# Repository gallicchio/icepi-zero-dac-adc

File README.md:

# FPGA tutorials: an ADC and a DAC on an Icepi Zero

A hands-on tutorial for a junior-level physics electronics lab. You should
know basic analog and digital electronics and a little Fourier analysis. You
do **not** need to have seen an [FPGA](https://en.wikipedia.org/wiki/Field-programmable_gate_array) or a hardware description language
before.

You will:

* configure the logic inside an FPGA to **blink lights**, **make analog
  waveforms** and **capture analog signals** at 25 million samples a second;
* build a **[lock-in amplifier](https://en.wikipedia.org/wiki/Lock-in_amplifier)** and use it as a simple [network analyzer](https://en.wikipedia.org/wiki/Network_analyzer_(electrical)), and
  a **[spectrum analyzer](https://en.wikipedia.org/wiki/Spectrum_analyzer)**, with an FFT computed in logic;
* build an **AM radio**, transmitter and receiver, and hear it on a real radio
  and on your laptop;
* turn the same FPGA into a **[RISC-V](https://en.wikipedia.org/wiki/RISC-V) computer** and write C programs that run
  on it and talk to your hardware;
* boot **Linux** on that computer, and read the [ADC](https://en.wikipedia.org/wiki/Analog-to-digital_converter) as an ordinary file;
* and then, if you like, keep going: crystals, resonators, the speed of sound,
  [time transfer](https://en.wikipedia.org/wiki/Time_transfer) between two boards (as national labs do it), modern
  digital communications (OFDM, at 56 Mbit/s through a cable), and a radio
  link.

Everything is open source, from the FPGA tools to the instruments: an
open-source function generator, digitizer (a slow oscilloscope), lock-in
amplifier, network analyzer, FFT spectrum analyzer, AM transmitter and
software-defined radio receiver, modems, and a time-transfer link, each a
page or two of SystemVerilog and Python that you can read and change.
[5.08](tutorial/5_08_more_hardware.md#instruments-for-a-physics-lab) lists more
that physics labs usually buy: a [Pound–Drever–Hall](https://en.wikipedia.org/wiki/Pound%E2%80%93Drever%E2%80%93Hall_technique) laser lock, a
coincidence counter, shot-noise and Johnson-noise measurements.

Most people will get as far as the lock-in amplifier
([1.08](tutorial/1_08_lockin.md#108-a-lock-in-amplifier)), and that's a fine
place to stop. Each later chapter builds on the earlier ones, but you can
skip around inside Chapters 4 and 5. The hardware is about $120:
[0.00](tutorial/0_00_the_hardware.md#000-the-hardware) has the list, and
[Appendix A](tutorial/A_why_this_hardware.md#appendix-a-why-this-hardware)
the prices.

**Start here: [0.00 The hardware](tutorial/0_00_the_hardware.md#000-the-hardware).**

## What depends on what

Nothing after Chapter 1 needs all of Chapter 1, and nothing needs Linux
except the two pages that use it. The spine is 1.00–1.08: the tools, a
counter, the [DAC](https://en.wikipedia.org/wiki/Digital-to-analog_converter), a sine, the ADC into Python, fast captures, the loopback,
and the lock-in. After that, go where you like:

```mermaid
flowchart LR
  spine["<b>Chapter 1, the spine</b><br/>1.00–1.08: tools, DAC, ADC,<br/>loopback, lock-in"]
  fft["1.09 FFT spectrum analyzer"]
  am["1.10 AM radio"]
  c2["<b>2. A processor</b><br/>LiteX, C, your peripherals"]
  c3["<b>3. Linux</b>"]
  c4["<b>4. One-board experiments</b><br/>(4.01 needs only 1.03)"]
  c5["<b>5. Two boards</b>"]
  c6["<b>6. Digital communications</b>"]
  c7["<b>7. Signal processing in gateware</b><br/>filters, delta-sigma, control"]
  spine --> fft
  spine --> am
  spine --> c2 --> c3
  spine --> c4
  spine --> c5
  spine --> c6
  spine --> c7
  c2 -. "7.04's LiteX peripheral" .-> c7
  c6 -. "6.11's modem is the warm-up" .-> c7
  fft -. "6.07's OFDM" .-> c6
  c5 -. "awgcap.sv: just load it (6.00)" .-> c6
  c5 -. "5.07's loops, for 6.12's air" .-> c6
  c5 -. "5.05's network between two Linuxes" .-> c3
  c2 -. "2.00's tool install, then 3.01 boots the prebuilt Linux" .-> c3
```

The shortest paths:

- **The lock-in amplifier:** 1.00–1.08. (1.04 is optional; 1.09 and 1.10 are desserts.)
- **Digital communications (Chapter 6):** the spine, then [6.00](tutorial/6_00_digital_communications.md#600-digital-communications-hardware-defined-radio). It uses one
  design from Chapter 5, `awgcap.sv`, which you load without reading the chapter. One board is enough.
- **Linux on the FPGA:** 1.00–1.01 (load a bitstream), [2.00](tutorial/2_00_a_processor_on_the_fpga.md#200-a-processor-on-the-fpga) (install LiteX), then
  [3.01](tutorial/3_01_booting_linux.md#301-booting-linux) boots the prebuilt images. Understanding the driver ([3.02](tutorial/3_02_a_driver.md#302-a-driver)) wants 2.03–2.05;
  building it all yourself ([3.03](tutorial/3_03_building_linux.md#303-building-linux-yourself)) wants Chapter 2.
- **Filters, delta-sigma and control (Chapter 7):** the spine, then [7.00](tutorial/7_00_signal_processing_in_gateware.md#700-signal-processing-in-gateware); 7.04 alone needs Chapter 2's tools.
- **The experiments (Chapter 4):** the spine; each page says which instrument it uses.
- **Two boards (Chapter 5):** the spine and a second board; only the network part of
  [5.05](tutorial/5_05_fsk_modem.md#505-a-modem) needs Chapter 3.

Every chapter opener (2.00, 3.00, 4.00, 5.00, 6.00) starts with "What you need
first", so you can check before you start.

## Related reading

- **[learnSDR](https://github.com/gallicchio/learnSDR)**, this author's video course in software-defined radio with
  GNU Radio: Chapter 6 links its lessons.
- **[PySDR](https://pysdr.org)**, Marc Lichtman's free online textbook of SDR and DSP in Python. It is
  better than these pages at the theory and the Python, and it covers what this tutorial
  can't (link budgets, beamforming, real SDR hardware); read it alongside Chapter 6. What
  this tutorial has that it doesn't is that the hardware is yours, down to the clock.
- **[MIT's coffee-can radar course](https://ocw.mit.edu/courses/res-ll-003-build-a-small-radar-system-capable-of-sensing-range-doppler-and-synthetic-aperture-radar-imaging-january-iap-2011/)**, the model for the radar chapter sketched in [6.13](tutorial/6_13_more_ideas.md#613-more-ideas-and-a-radar-chapter).

## Contents

**0. Getting started**

- [0.00 The hardware](tutorial/0_00_the_hardware.md)
- [0.01 How to use this tutorial](tutorial/0_01_how_to_use_this_tutorial.md)

**1. Logic in [SystemVerilog](https://en.wikipedia.org/wiki/SystemVerilog), up to a lock-in amplifier and an FFT**

- [1.00 Circuits from code](tutorial/1_00_circuits_from_code.md)
- [1.01 A counter on the LEDs](tutorial/1_01_led_counter.md)
- [1.02 A sawtooth from the DAC](tutorial/1_02_dac_sawtooth.md)
- [1.03 A sine: direct digital synthesis](tutorial/1_03_dac_sine.md)
- [1.04 The ADC on the LEDs](tutorial/1_04_adc_on_the_leds.md)
- [1.05 ADC samples to Python](tutorial/1_05_adc_to_python.md)
- [1.06 Fast captures](tutorial/1_06_fast_capture.md)
- [1.07 Closing the loop: the DAC talks to the ADC](tutorial/1_07_closing_the_loop.md)
- [1.08 A lock-in amplifier](tutorial/1_08_lockin.md)
- [1.09 A spectrum analyzer](tutorial/1_09_spectrum_analyzer.md)
- [1.10 An AM radio](tutorial/1_10_am_radio.md)

**2. A RISC-V processor, and C**

- [2.00 A processor on the FPGA](tutorial/2_00_a_processor_on_the_fpga.md)
- [2.01 A CPU and its BIOS](tutorial/2_01_a_cpu_and_its_bios.md)
- [2.02 C on the CPU](tutorial/2_02_c_on_the_cpu.md)
- [2.03 A function-generator peripheral](tutorial/2_03_function_generator_peripheral.md)
- [2.04 A capture peripheral](tutorial/2_04_capture_peripheral.md)
- [2.05 A lock-in peripheral](tutorial/2_05_lockin_peripheral.md)
- [2.06 The registers from the laptop](tutorial/2_06_registers_from_the_laptop.md)

**3. Linux**

- [3.00 Linux on the FPGA](tutorial/3_00_linux_on_the_fpga.md)
- [3.01 Booting Linux](tutorial/3_01_booting_linux.md)
- [3.02 A driver](tutorial/3_02_a_driver.md)
- [3.03 Building Linux yourself](tutorial/3_03_building_linux.md)
- [3.04 Booting from an SD card](tutorial/3_04_booting_from_sd.md)

**4. More experiments with one board**

- [4.00 One-board experiments](tutorial/4_00_one_board_experiments.md)
- [4.01 A faster DAC: PLLs](tutorial/4_01_a_faster_dac.md)
- [4.02 RC and LC circuits](tutorial/4_02_rc_and_lc_circuits.md)
- [4.03 The Q of a quartz crystal](tutorial/4_03_quartz_crystal.md)
- [4.04 Harmonics: a diode clipper](tutorial/4_04_harmonics.md)
- [4.05 A quarter-wave stub](tutorial/4_05_quarter_wave_stub.md)
- [4.06 The speed of sound at 40 kHz](tutorial/4_06_speed_of_sound.md)
- [4.07 An optical link](tutorial/4_07_optical_link.md)
- [4.08 Feedback control of an RC plant](tutorial/4_08_feedback_control.md)
- [4.09 Your crystal against a reference](tutorial/4_09_your_crystal.md)
- [4.10 More ideas for one board](tutorial/4_10_more_ideas.md)

**5. Two boards**

- [5.00 Two boards on one laptop](tutorial/5_00_two_boards.md)
- [5.01 Two clocks](tutorial/5_01_two_clocks.md)
- [5.02 Warming a crystal](tutorial/5_02_warming_a_crystal.md)
- [5.03 What time is it over there?](tutorial/5_03_time_transfer.md)
- [5.04 Oscillators that listen to each other](tutorial/5_04_coupled_oscillators.md)
- [5.05 A modem](tutorial/5_05_fsk_modem.md)
- [5.06 The modem against noise](tutorial/5_06_modem_and_noise.md)
- [5.07 A radio link](tutorial/5_07_radio_link.md)
- [5.08 With a little more hardware](tutorial/5_08_more_hardware.md)

**6. Digital communications (Hardware Defined Radio)**

- [6.00 Digital communications (Hardware Defined Radio)](tutorial/6_00_digital_communications.md)
- [6.01 Eye diagrams and pulse shaping](tutorial/6_01_eye_diagrams.md)
- [6.02 PSK and QPSK: finding the clock and the carrier](tutorial/6_02_psk_and_qpsk.md)
- [6.03 QAM: more bits per symbol](tutorial/6_03_qam.md)
- [6.04 MSK and GMSK: constant envelope](tutorial/6_04_msk_and_gmsk.md)
- [6.05 The channel: sounding it, and equalizing it](tutorial/6_05_the_channel.md)
- [6.06 Spread spectrum, the GPS way](tutorial/6_06_spread_spectrum.md)
- [6.07 OFDM: the triumph of physics over math](tutorial/6_07_ofdm.md)
- [6.08 Shannon's limit, and how far from it you are](tutorial/6_08_shannons_limit.md)
- [6.09 Error-correcting codes](tutorial/6_09_error_correcting_codes.md)
- [6.10 Chirps, Zadoff–Chu and LoRa: ranging, and radar on a cable](tutorial/6_10_chirps_and_lora.md)
- [6.11 The modem in the FPGA](tutorial/6_11_the_modem_in_the_fpga.md)
- [6.12 On the air: whispers, and how far they carry](tutorial/6_12_on_the_air.md)
- [6.13 More ideas, and a radar chapter](tutorial/6_13_more_ideas.md)

**7. Signal processing in gateware**

- [7.00 Signal processing in gateware](tutorial/7_00_signal_processing_in_gateware.md)
- [7.01 FIR filters: the sliding dot product](tutorial/7_01_fir_filters.md)
- [7.02 IIR filters: feedback, and an RC in one line](tutorial/7_02_iir_filters.md)
- [7.03 A filter you can load](tutorial/7_03_a_filter_you_can_load.md)
- [7.04 The filter as a LiteX peripheral](tutorial/7_04_the_filter_as_a_litex_peripheral.md)
- [7.05 Trading speed for bits](tutorial/7_05_trading_speed_for_bits.md)
- [7.06 Control at the speed of the cable](tutorial/7_06_control.md)
- [7.07 Bigger ideas: NMR, MRI and qubits](tutorial/7_07_bigger_ideas.md)

**Appendices**

- [Appendix A. Why this hardware?](tutorial/A_why_this_hardware.md)
- [Appendix B. Troubleshooting](tutorial/B_troubleshooting.md)
- [Appendix C. How this tutorial was tested](tutorial/C_how_it_was_tested.md)
- [Appendix D. Coming soon… hopefully](tutorial/D_coming_soon.md)

## What's in this repository

| folder | what |
| --- | --- |
| [`tutorial/`](tutorial/) | the tutorial, one page per topic, in order |
| [`src/`](src/) | everything you build: [`verilog/`](src/verilog/) (Chapters 1 and 4), [`riscv/`](src/riscv/) (Chapter 2), [`linux/`](src/linux/) (Chapter 3), [`twoboard/`](src/twoboard/) (Chapter 5, and 6.11's `qpsk_modem.sv` and 6.12's `ddc.sv`), [`comms/`](src/comms/) (Chapter 6's Python), [`dsp/`](src/dsp/) (Chapter 7) |
| [`adapter_board/`](adapter_board/) | the adapter PCB between the Icepi Zero and the converter module: KiCad files and gerbers, ready to order |
| [`dev/`](dev/) | how the tutorial was made and tested: measurement scripts, raw data, and the log of the Claude Code sessions that wrote it |
| [`LICENSE`](LICENSE), [`LICENSES/`](LICENSES/) | which licence covers what, and their full texts |
| `tools/` | not in the repository: you make it in [1.00](tutorial/1_00_circuits_from_code.md#100-circuits-from-code), and the tools you install go there. Git ignores it |

Every design, script, figure and number in the tutorial comes from the real
hardware; [Appendix C](tutorial/C_how_it_was_tested.md) says how.

## Licence

The tutorial (text, figures and data) is under [CC BY 4.0](LICENSES/CC-BY-4.0.txt), the
code under [MIT](LICENSES/MIT.txt), the Linux driver under
[GPL-2.0](LICENSES/GPL-2.0-only.txt) and the adapter board under
[CERN-OHL-P-2.0](LICENSES/CERN-OHL-P-2.0.txt). The prebuilt Linux images keep their
components' licences. [LICENSE](LICENSE) has the details.

*By [Jason Gallicchio](mailto:jason@hmc.edu) (jason@hmc.edu), Physics Professor at
Harvey Mudd College, written along with Claude (Opus 5.5 and Fable 5.1), which also
ran every measurement: Appendix C says how.* I (Jason) wrote more of the very early
stuff and then got carried away when I let Claude take over,
eventually pushing it to write my dream tutorial.
I'll eventually work to remove the slop, but one advantage of this is that the LLMs
can clone this repo and really walk you through the material in a way that might
be more difficult otherwise.
One might sell this as "Created with the help of AI to help AI help you."  (AI obviously didn't write that one.)
After a long weekend of editing and prompting, there's suddenly a two or three-semester course here.
See [dev/CLAUDE_CODE_CHAT.md](dev/CLAUDE_CODE_CHAT.md) for most of the chat.

*Dedicated to the memory of Brian Bryce's years at Harvey Mudd, where he showed a department that open tools and open hardware are how you do interesting physics and engineering without asking for anyone's permission or spending anyone's money. He isn't gone, just elsewhere, and this is the kind of thing he'd have liked.*

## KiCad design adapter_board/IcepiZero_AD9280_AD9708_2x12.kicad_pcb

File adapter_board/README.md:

# The adapter board

A passive 65 × 30 mm board that connects an Icepi Zero's 40-pin header to the
AD9280/AD9708 converter module with a 2×12 header and SMA connectors (the one in
the tutorial's photo).

## Ordering it

Upload `IcepiZero_AD9280_AD9708_2x12-gerbers.zip` to a PCB maker such as
[JLCPCB](https://jlcpcb.com/), keep the defaults (2 layers, 1.6 mm, any
colour), and ask for as many boards as you need. Five cost about $2 plus
shipping.

Then solder on:

| part | what | where |
| --- | --- | --- |
| J1 | 2×20 female socket, 2.54 mm | on the **bottom**: it takes the Icepi Zero's 40-pin header |
| J2 | 2×12 male header, 2.54 mm | on the top, pins up: the module's socket plugs onto it |
| C1, C2 | 10 µF (0805) and 100 nF (0603) capacitors | the module's 5 V supply; optional |
| GND1, GND2 | plated holes | for a wire to the module's own ground, if you want a better ground return than the headers give |

## Plugging it together

The adapter has the Icepi Zero's shape, and the mounting holes of the two line
up. Plug the Icepi Zero in so that they do. **The wrong way round puts 5 V on
FPGA pins.**

The module goes on top. Every pin of both connectors is named on the
silkscreen, with the same names the module uses (`AD0`...`AD7` and `ACLK` for the
ADC, `DA0`...`DA7` and `DCLK` for the DAC), so line the module's labels up with
J2's.

## Files

The KiCad 10 project (`.kicad_pro`, `.kicad_sch`, `.kicad_pcb`), the schematic
as a PDF, the gerbers, a picture, and the pin map:

| module pin | design name | Icepi Zero header pin | Raspberry Pi name | ECP5 ball |
| --- | --- | --- | --- | --- |
| AD0 ... AD7 | `adc_d[0]` ... `adc_d[7]` | 7, 11, 12, 13, 15, 16, 18, 19 | GPIO4, 17, 18, 27, 22, 23, 24, 10 | R1, R3, N4, P3, P2, M2, L1, L2 |
| ACLK | `adc_clk` | 21 | GPIO9 | J1 |
| DCLK | `dac_clk` | 23 | GPIO11 | G2 |
| DA7 ... DA0 | `dac_d[7]` ... `dac_d[0]` | 24, 26, 29, 31, 32, 33, 35, 37 | GPIO8, 7, 5, 6, 12, 13, 19, 26 | H2, G1, E1, F3, J3, E3, E4, D4 |

The pin assignment stays off the six Raspberry Pi GPIOs that a real Pi can't
lend out (the HAT ID pins, I2C1 with its fixed pull-ups, and the serial
console), so the same adapter and module also plug into a Raspberry Pi, for a
much slower version of the same experiments.

The boards were drawn by a script, and the `.kicad_pcb` files are the source
of truth. The gerbers were plotted on 2026-09-14; plot new ones with KiCad
(*File → Fabrication Outputs*) if you change anything.

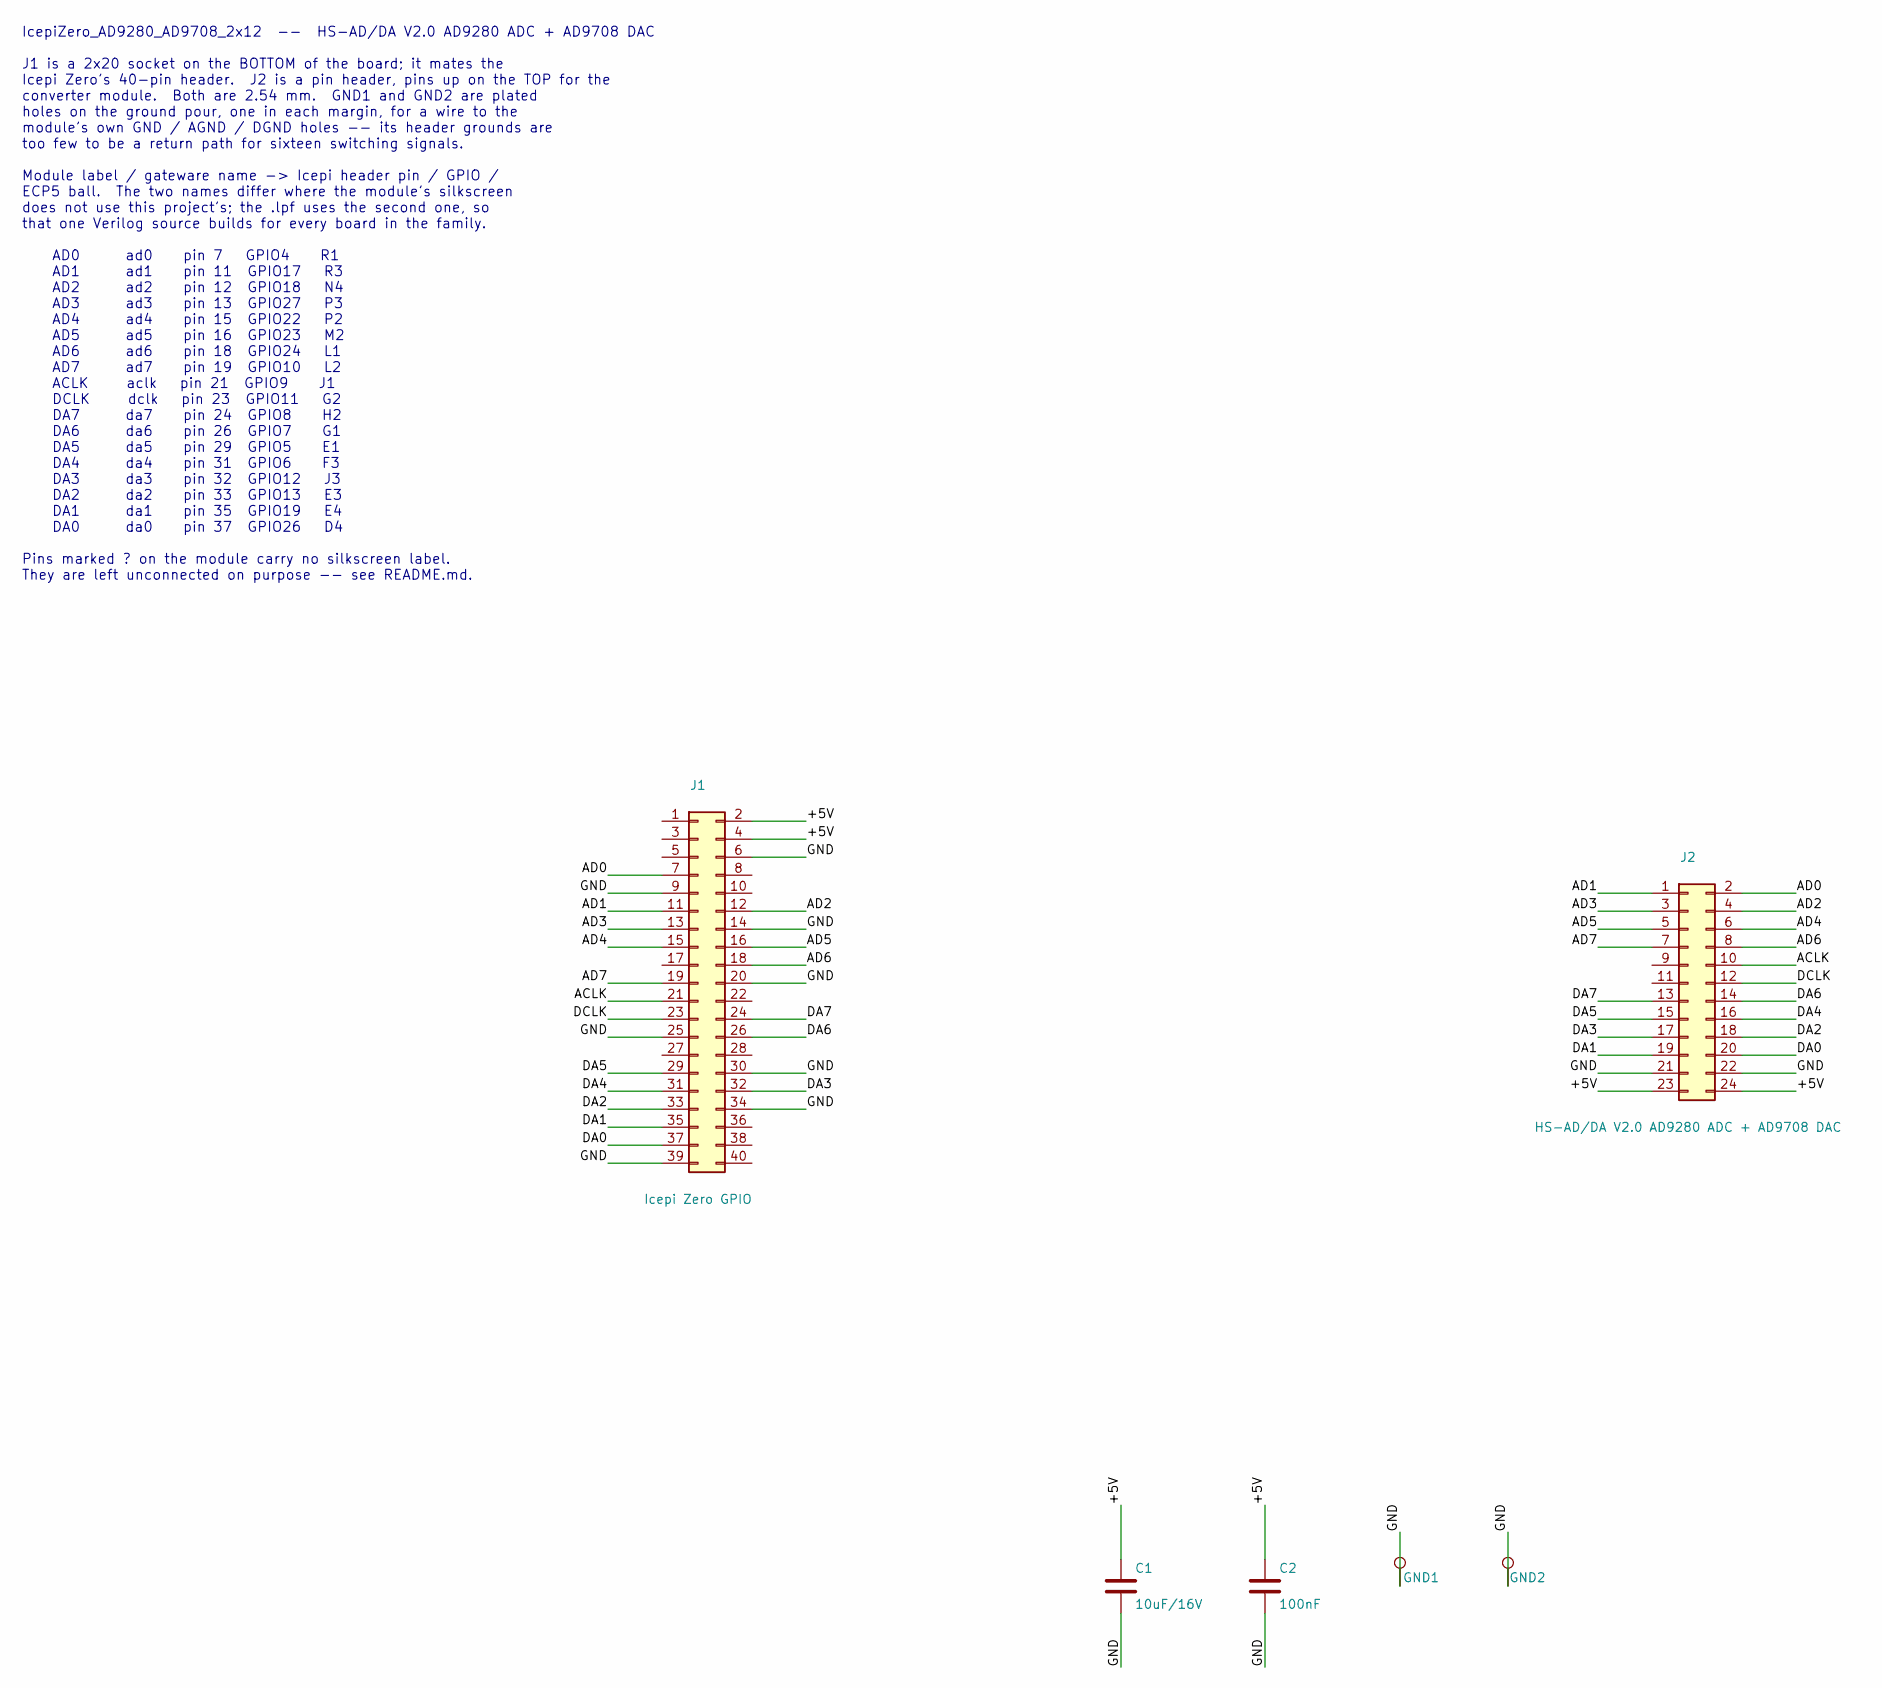
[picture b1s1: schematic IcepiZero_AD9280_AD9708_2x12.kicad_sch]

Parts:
C1: 10uF/16V; C_0805_2012Metric
C2: 100nF; C_0603_1608Metric
GND1, GND2: GND; TestPoint_THTPad_1.5x1.5mm_Drill0.7mm
J1: Icepi Zero GPIO; PinSocket_2x20_P2.54mm_Vertical
J2: HS-AD/DA V2.0 AD9280 ADC + AD9708 DAC; PinHeader_2x12_P2.54mm_Vertical

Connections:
+5V: C1.1, C2.1, J1.2, J1.4, J2.23, J2.24
ACLK: J1.21, J2.10
AD0: J1.7, J2.2
AD1: J1.11, J2.1
AD2: J1.12, J2.4
AD3: J1.13, J2.3
AD4: J1.15, J2.6
AD5: J1.16, J2.5
AD6: J1.18, J2.8
AD7: J1.19, J2.7
DA0: J1.37, J2.20
DA1: J1.35, J2.19
DA2: J1.33, J2.18
DA3: J1.32, J2.17
DA4: J1.31, J2.16
DA5: J1.29, J2.15
DA6: J1.26, J2.14
DA7: J1.24, J2.13
DCLK: J1.23, J2.12
GND: C1.2, C2.2, GND1.1, GND2.1, J1.6, J1.9, J1.14, J1.20, J1.25, J1.30, J1.34, J1.39, J2.21, J2.22

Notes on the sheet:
IcepiZero_AD9280_AD9708_2x12 -- HS-AD/DA V2.0 AD9280 ADC + AD9708 DAC J1 is a 2x20 socket on the BOTTOM of the board; it mates the Icepi Zero's 40-pin header. J2 is a pin header, pins up on the TOP for the converter module. Both are 2.54 mm. GND1 and GND2 are plated holes on the ground pour, one in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

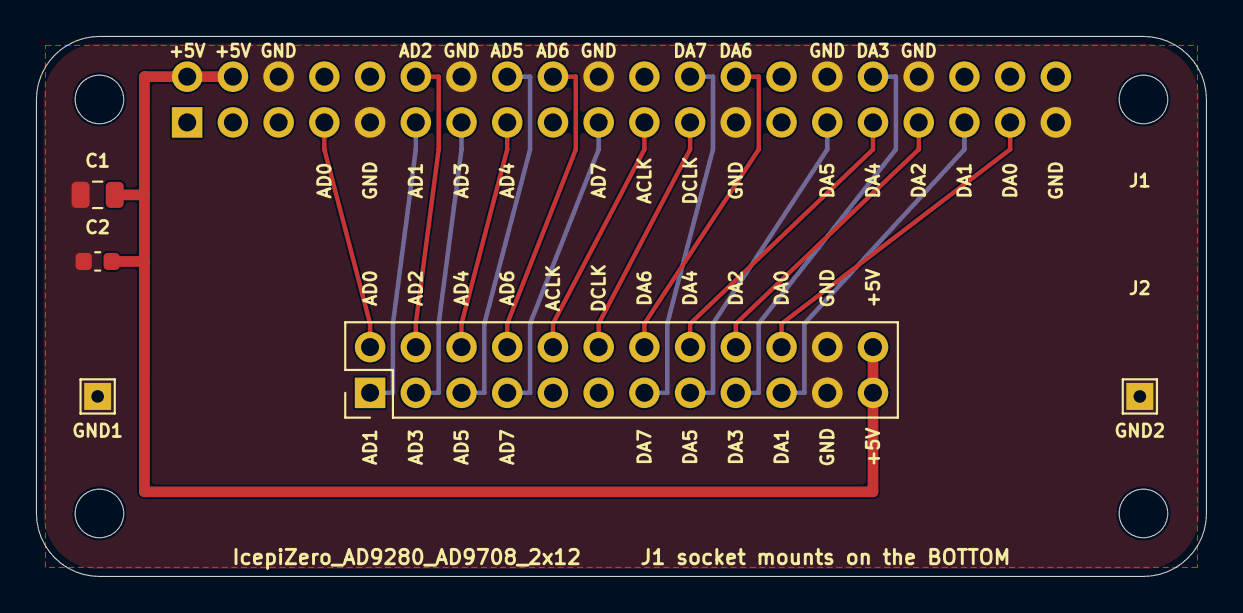
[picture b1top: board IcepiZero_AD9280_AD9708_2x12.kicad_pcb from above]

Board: 2 copper layers, 65.0 x 30.0 mm, 10 parts (1 on the bottom side), 20 nets.

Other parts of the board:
H1, H2, H3, H4: M2.5; MountingHole_2.7mm_M2.5_ISO7380
